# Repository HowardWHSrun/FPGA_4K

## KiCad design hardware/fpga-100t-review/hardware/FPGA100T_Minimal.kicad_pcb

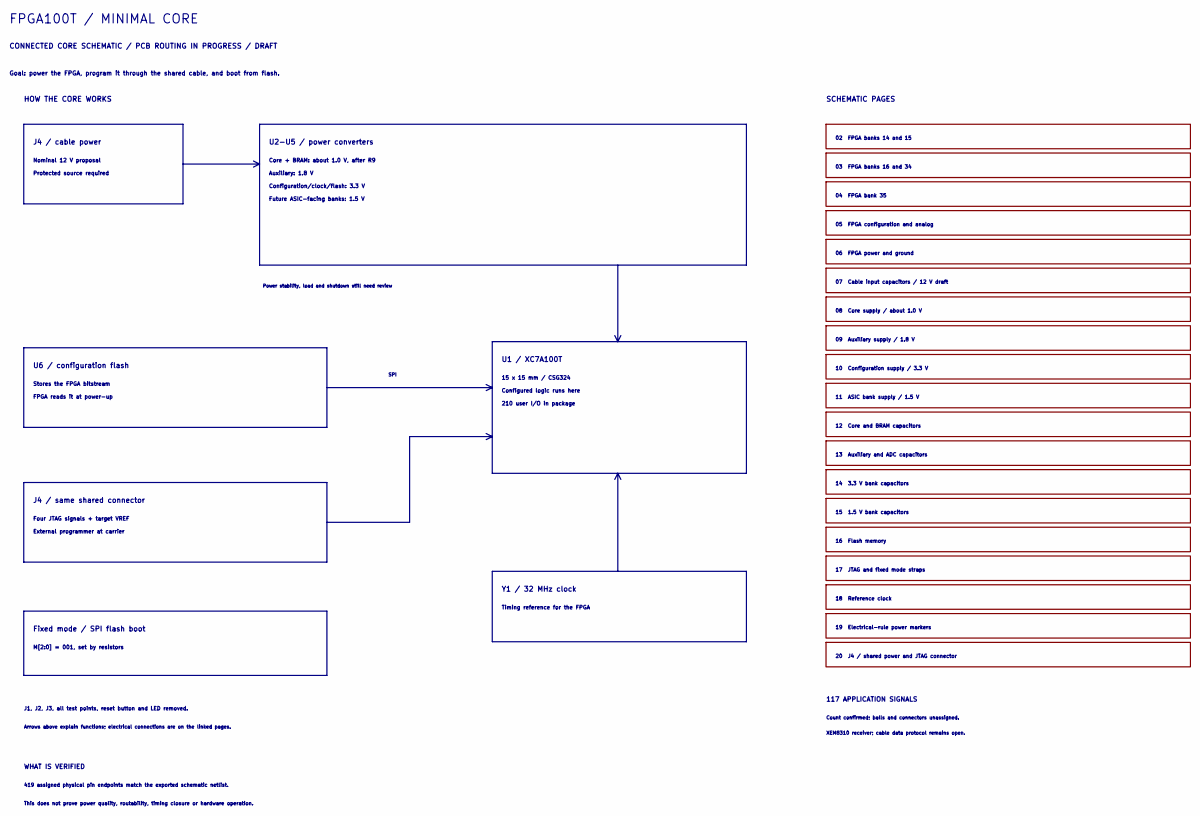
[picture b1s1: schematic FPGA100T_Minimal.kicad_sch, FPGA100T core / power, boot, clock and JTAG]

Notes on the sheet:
FPGA100T / MINIMAL CORE
CONNECTED CORE SCHEMATIC / PCB ROUTING IN PROGRESS / DRAFT
Goal: power the FPGA, program it through the shared cable, and boot from flash.
HOW THE CORE WORKS
J4 / cable power
Nominal 12 V proposal
Protected source required
U2-U5 / power converters
Core + BRAM: about 1.0 V, after R9
Auxiliary: 1.8 V
Configuration/clock/flash: 3.3 V
Future ASIC-facing banks: 1.5 V
Power stability, load and shutdown still need review
U1 / XC7A100T
15 x 15 mm / CSG324
Configured logic runs here
210 user I/O in package
U6 / configuration flash
Stores the FPGA bitstream
FPGA reads it at power-up
SPI
J4 / same shared connector
Four JTAG signals + target VREF
External programmer at carrier
Y1 / 32 MHz clock
Timing reference for the FPGA
Fixed mode / SPI flash boot
M[2:0] = 001, set by resistors
J1, J2, J3, all test points, reset button and LED removed.
Arrows above explain functions; electrical connections are on the linked pages.
WHAT IS VERIFIED
419 assigned physical pin endpoints match the exported schematic netlist.
This does not prove power quality, routability, timing closure or hardware operation.
SCHEMATIC PAGES
02 FPGA banks 14 and 15
03 FPGA banks 16 and 34
04 FPGA bank 35
05 FPGA configuration and analog
06 FPGA power and ground
07 Cable input capacitors / 12 V draft

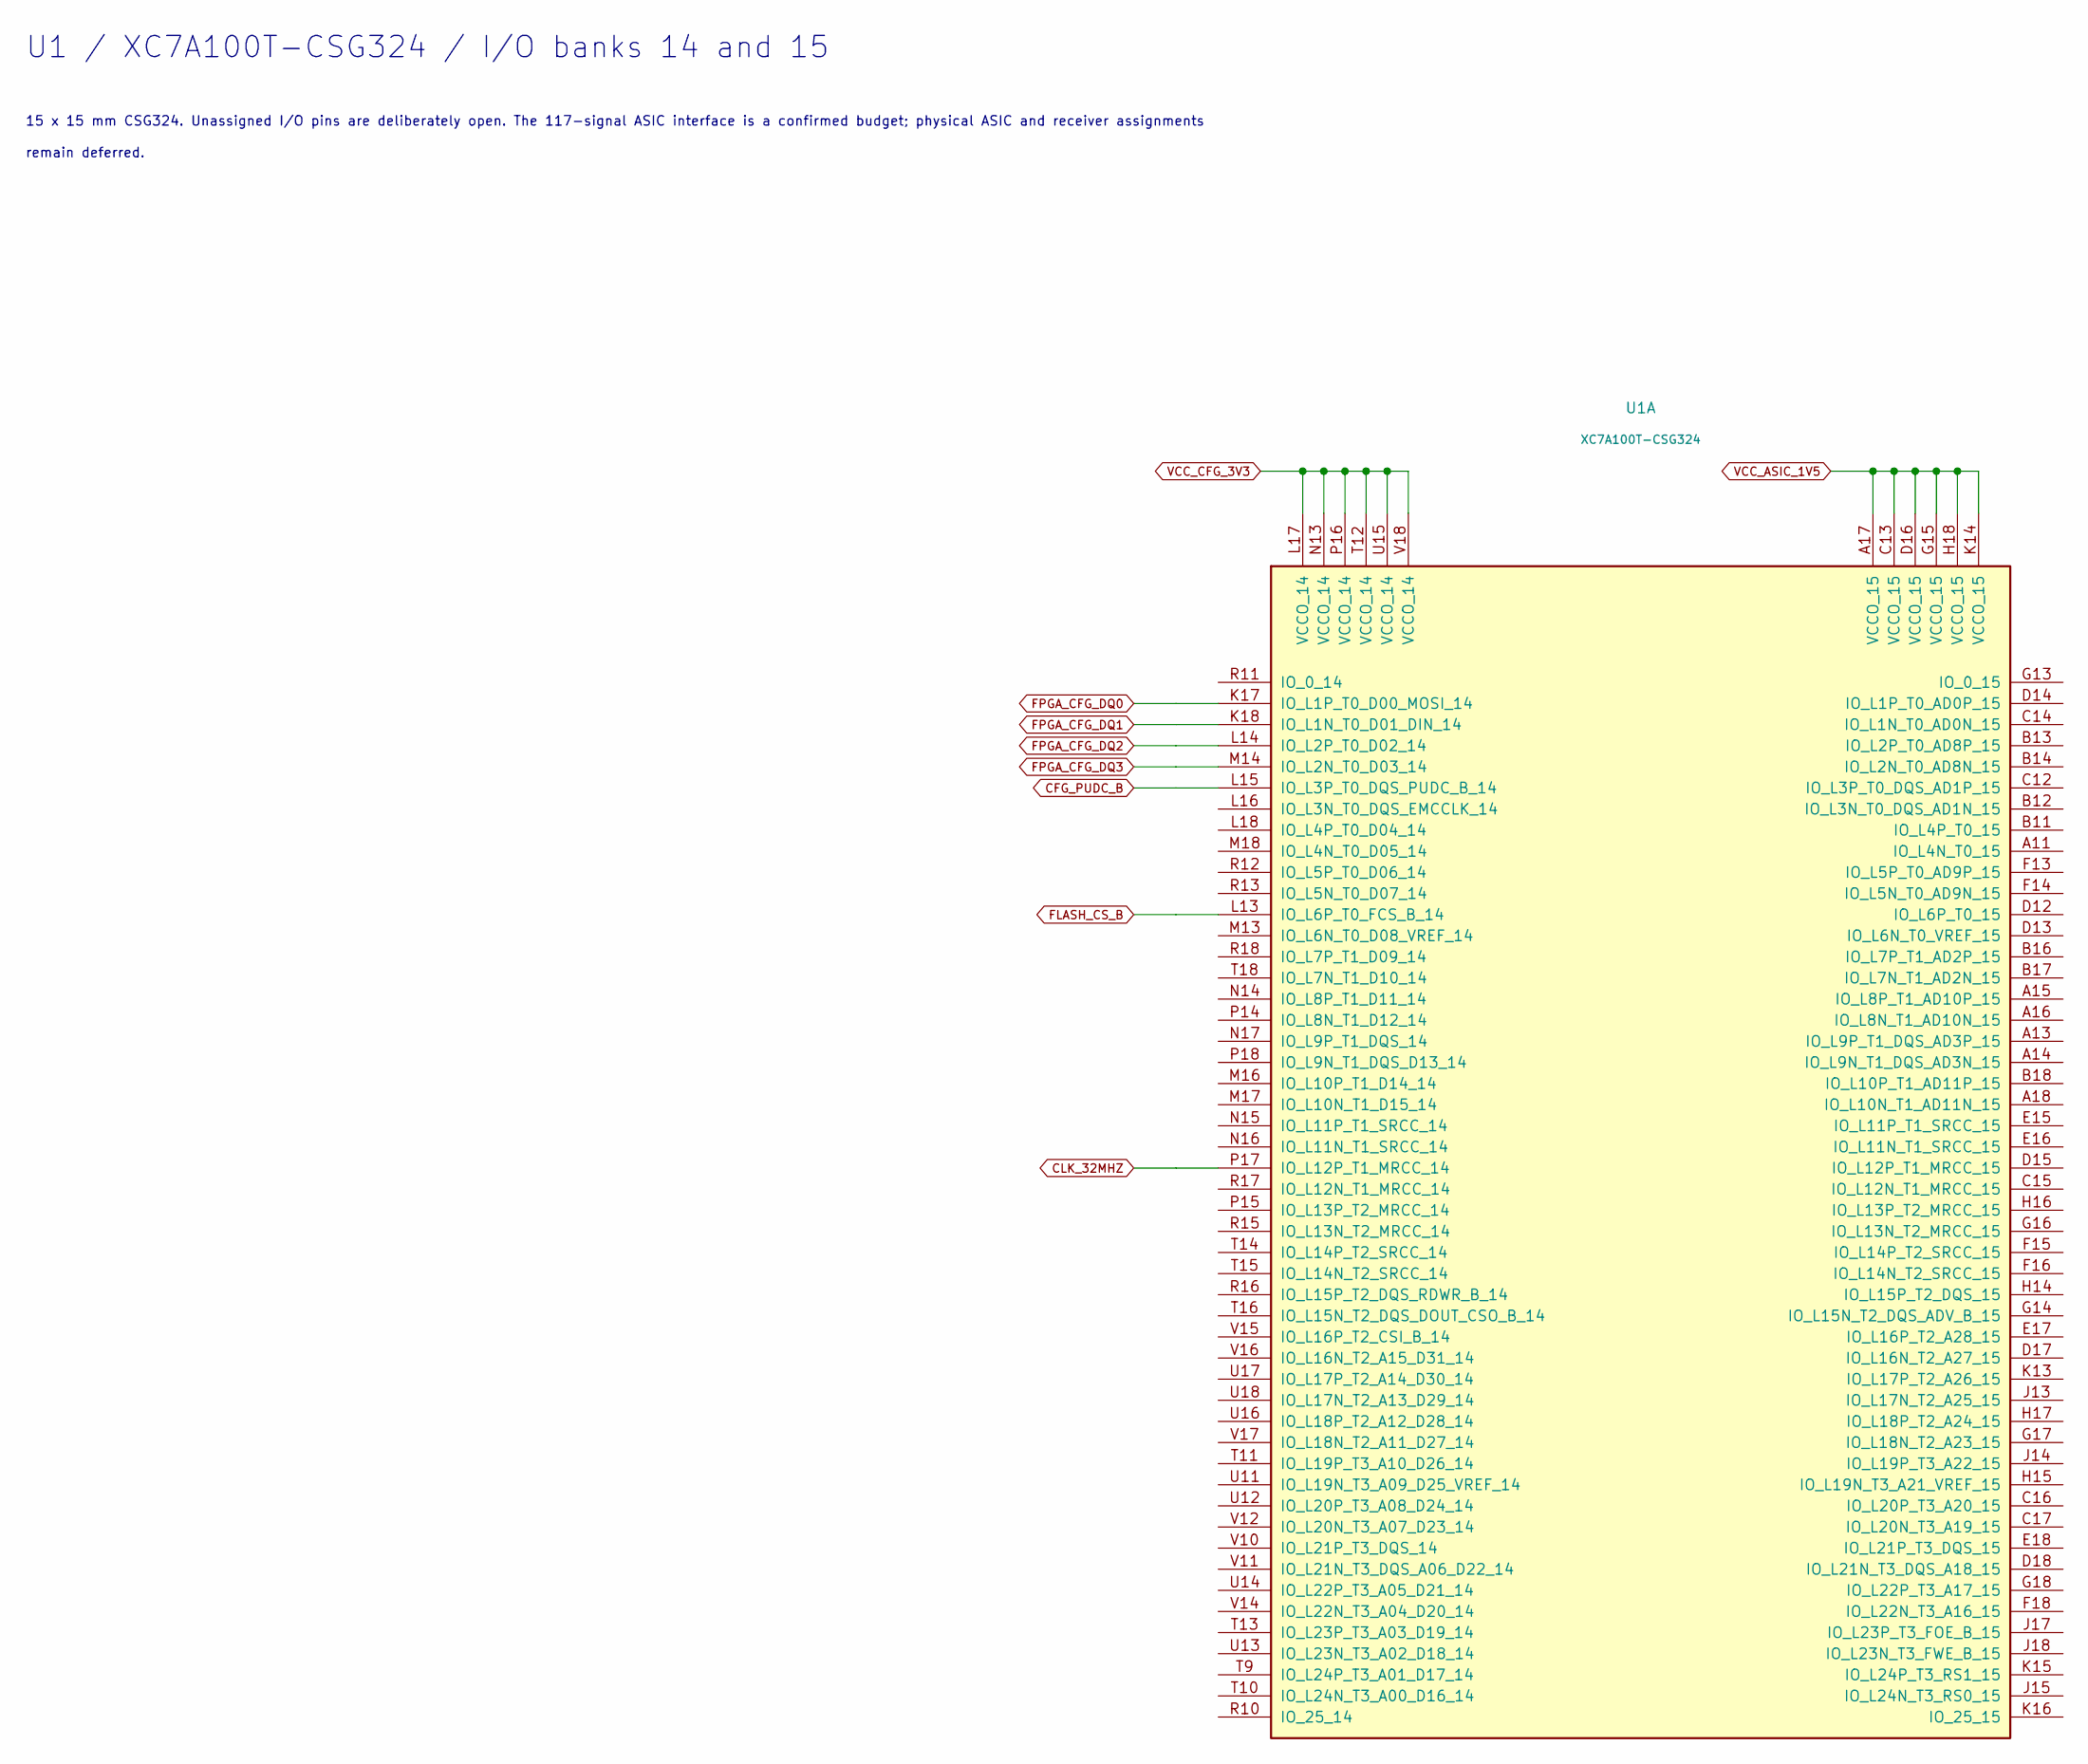
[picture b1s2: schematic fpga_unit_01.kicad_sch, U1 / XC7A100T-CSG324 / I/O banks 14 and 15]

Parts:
U1: XC7A100T-CSG324; Xilinx_CSG324; MPN XC7A100T — speed and temperature grade 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

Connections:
CFG_PUDC_B: U1.L15 (IO_L3P_T0_DQS_PUDC_B_14); also elsewhere on the board
CLK_32MHZ: U1.P17 (IO_L12P_T1_MRCC_14); also elsewhere on the board
FLASH_CS_B: U1.L13 (IO_L6P_T0_FCS_B_14); also elsewhere on the board
FPGA_CFG_DQ0: U1.K17 (IO_L1P_T0_D00_MOSI_14); also elsewhere on the board
FPGA_CFG_DQ1: U1.K18 (IO_L1N_T0_D01_DIN_14); also elsewhere on the board
FPGA_CFG_DQ2: U1.L14 (IO_L2P_T0_D02_14); also elsewhere on the board
FPGA_CFG_DQ3: U1.M14 (IO_L2N_T0_D03_14); also elsewhere on the board
VCC_ASIC_1V5: U1.A17 (VCCO_15), U1.C13 (VCCO_15), U1.D16 (VCCO_15), U1.G15 (VCCO_15), U1.H18 (VCCO_15), U1.K14 (VCCO_15); also elsewhere on the board
VCC_CFG_3V3: U1.L17 (VCCO_14), U1.N13 (VCCO_14), U1.P16 (VCCO_14), U1.T12 (VCCO_14), U1.U15 (VCCO_14), U1.V18 (VCCO_14); also elsewhere on the board

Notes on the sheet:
U1 / XC7A100T-CSG324 / I/O banks 14 and 15
15 x 15 mm CSG324. Unassigned I/O pins are deliberately open. The 117-signal ASIC interface is a confirmed budget; physical ASIC and receiver assignments
remain deferred.

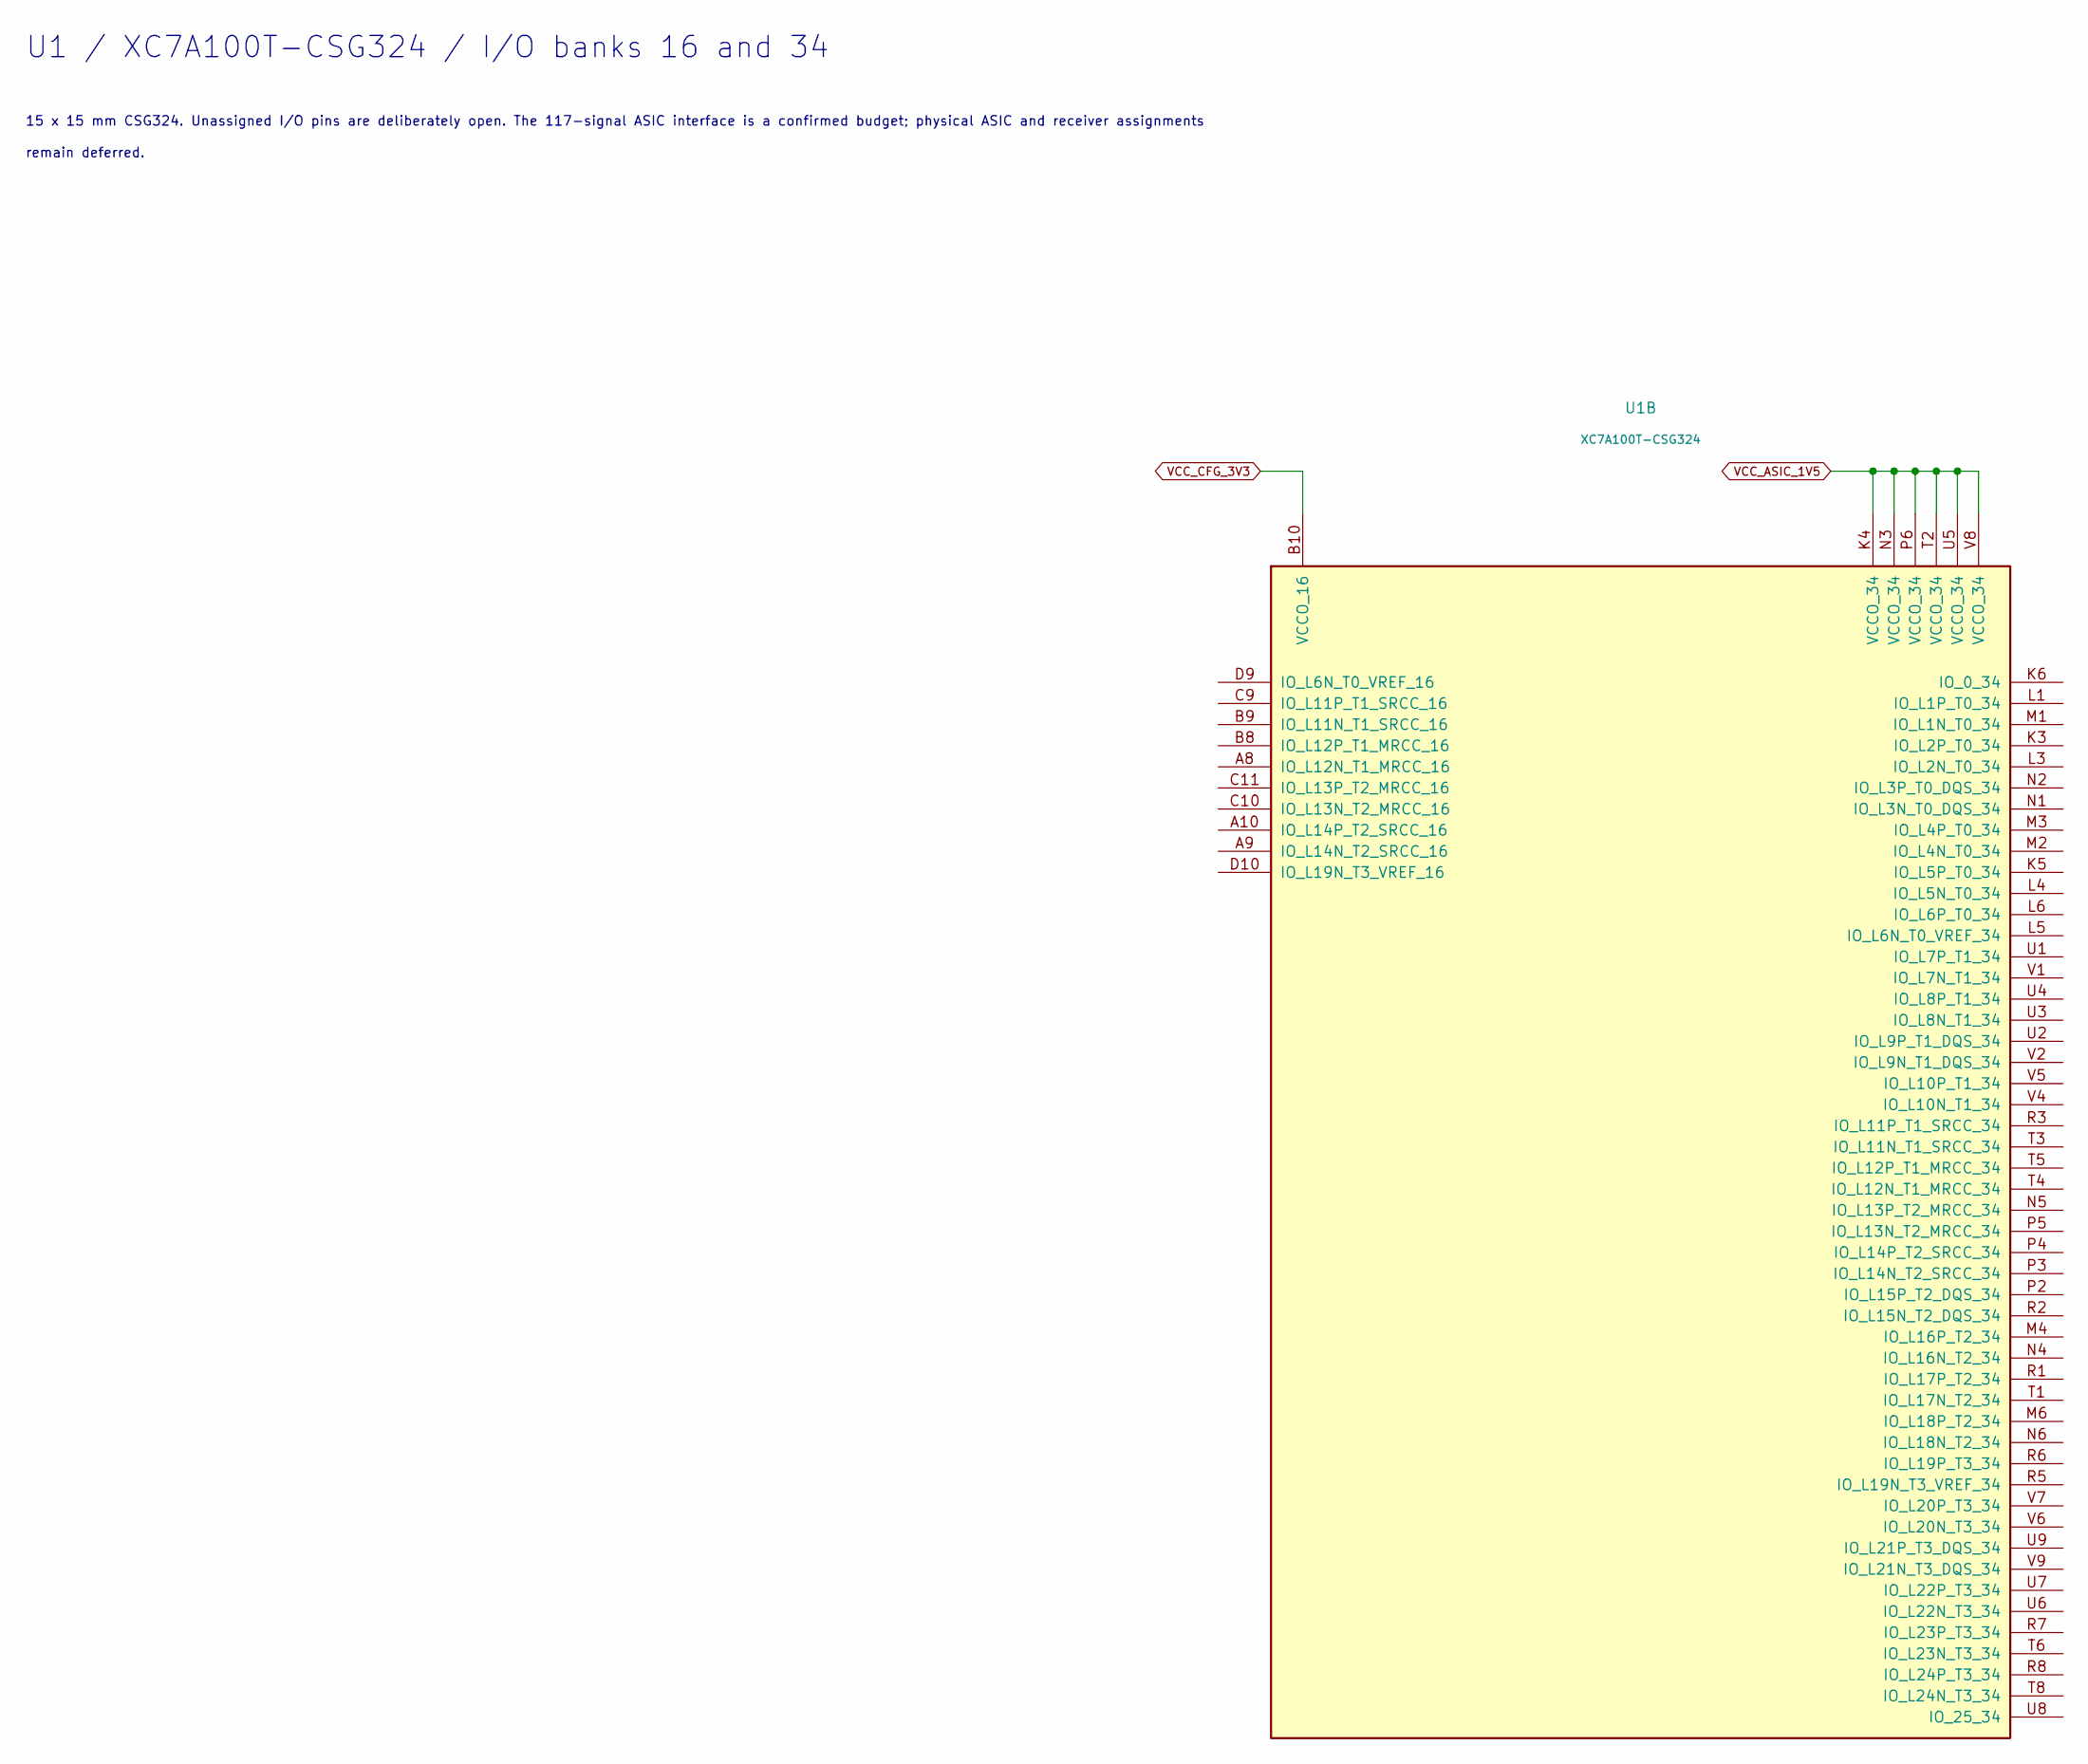
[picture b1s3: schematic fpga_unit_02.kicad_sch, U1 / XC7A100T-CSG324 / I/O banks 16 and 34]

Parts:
U1: XC7A100T-CSG324; Xilinx_CSG324; MPN XC7A100T — speed and temperature grade 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

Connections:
VCC_ASIC_1V5: U1.K4 (VCCO_34), U1.N3 (VCCO_34), U1.P6 (VCCO_34), U1.T2 (VCCO_34), U1.U5 (VCCO_34), U1.V8 (VCCO_34); also elsewhere on the board
VCC_CFG_3V3: U1.B10 (VCCO_16); also elsewhere on the board

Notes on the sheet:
U1 / XC7A100T-CSG324 / I/O banks 16 and 34
15 x 15 mm CSG324. Unassigned I/O pins are deliberately open. The 117-signal ASIC interface is a confirmed budget; physical ASIC and receiver assignments
remain deferred.

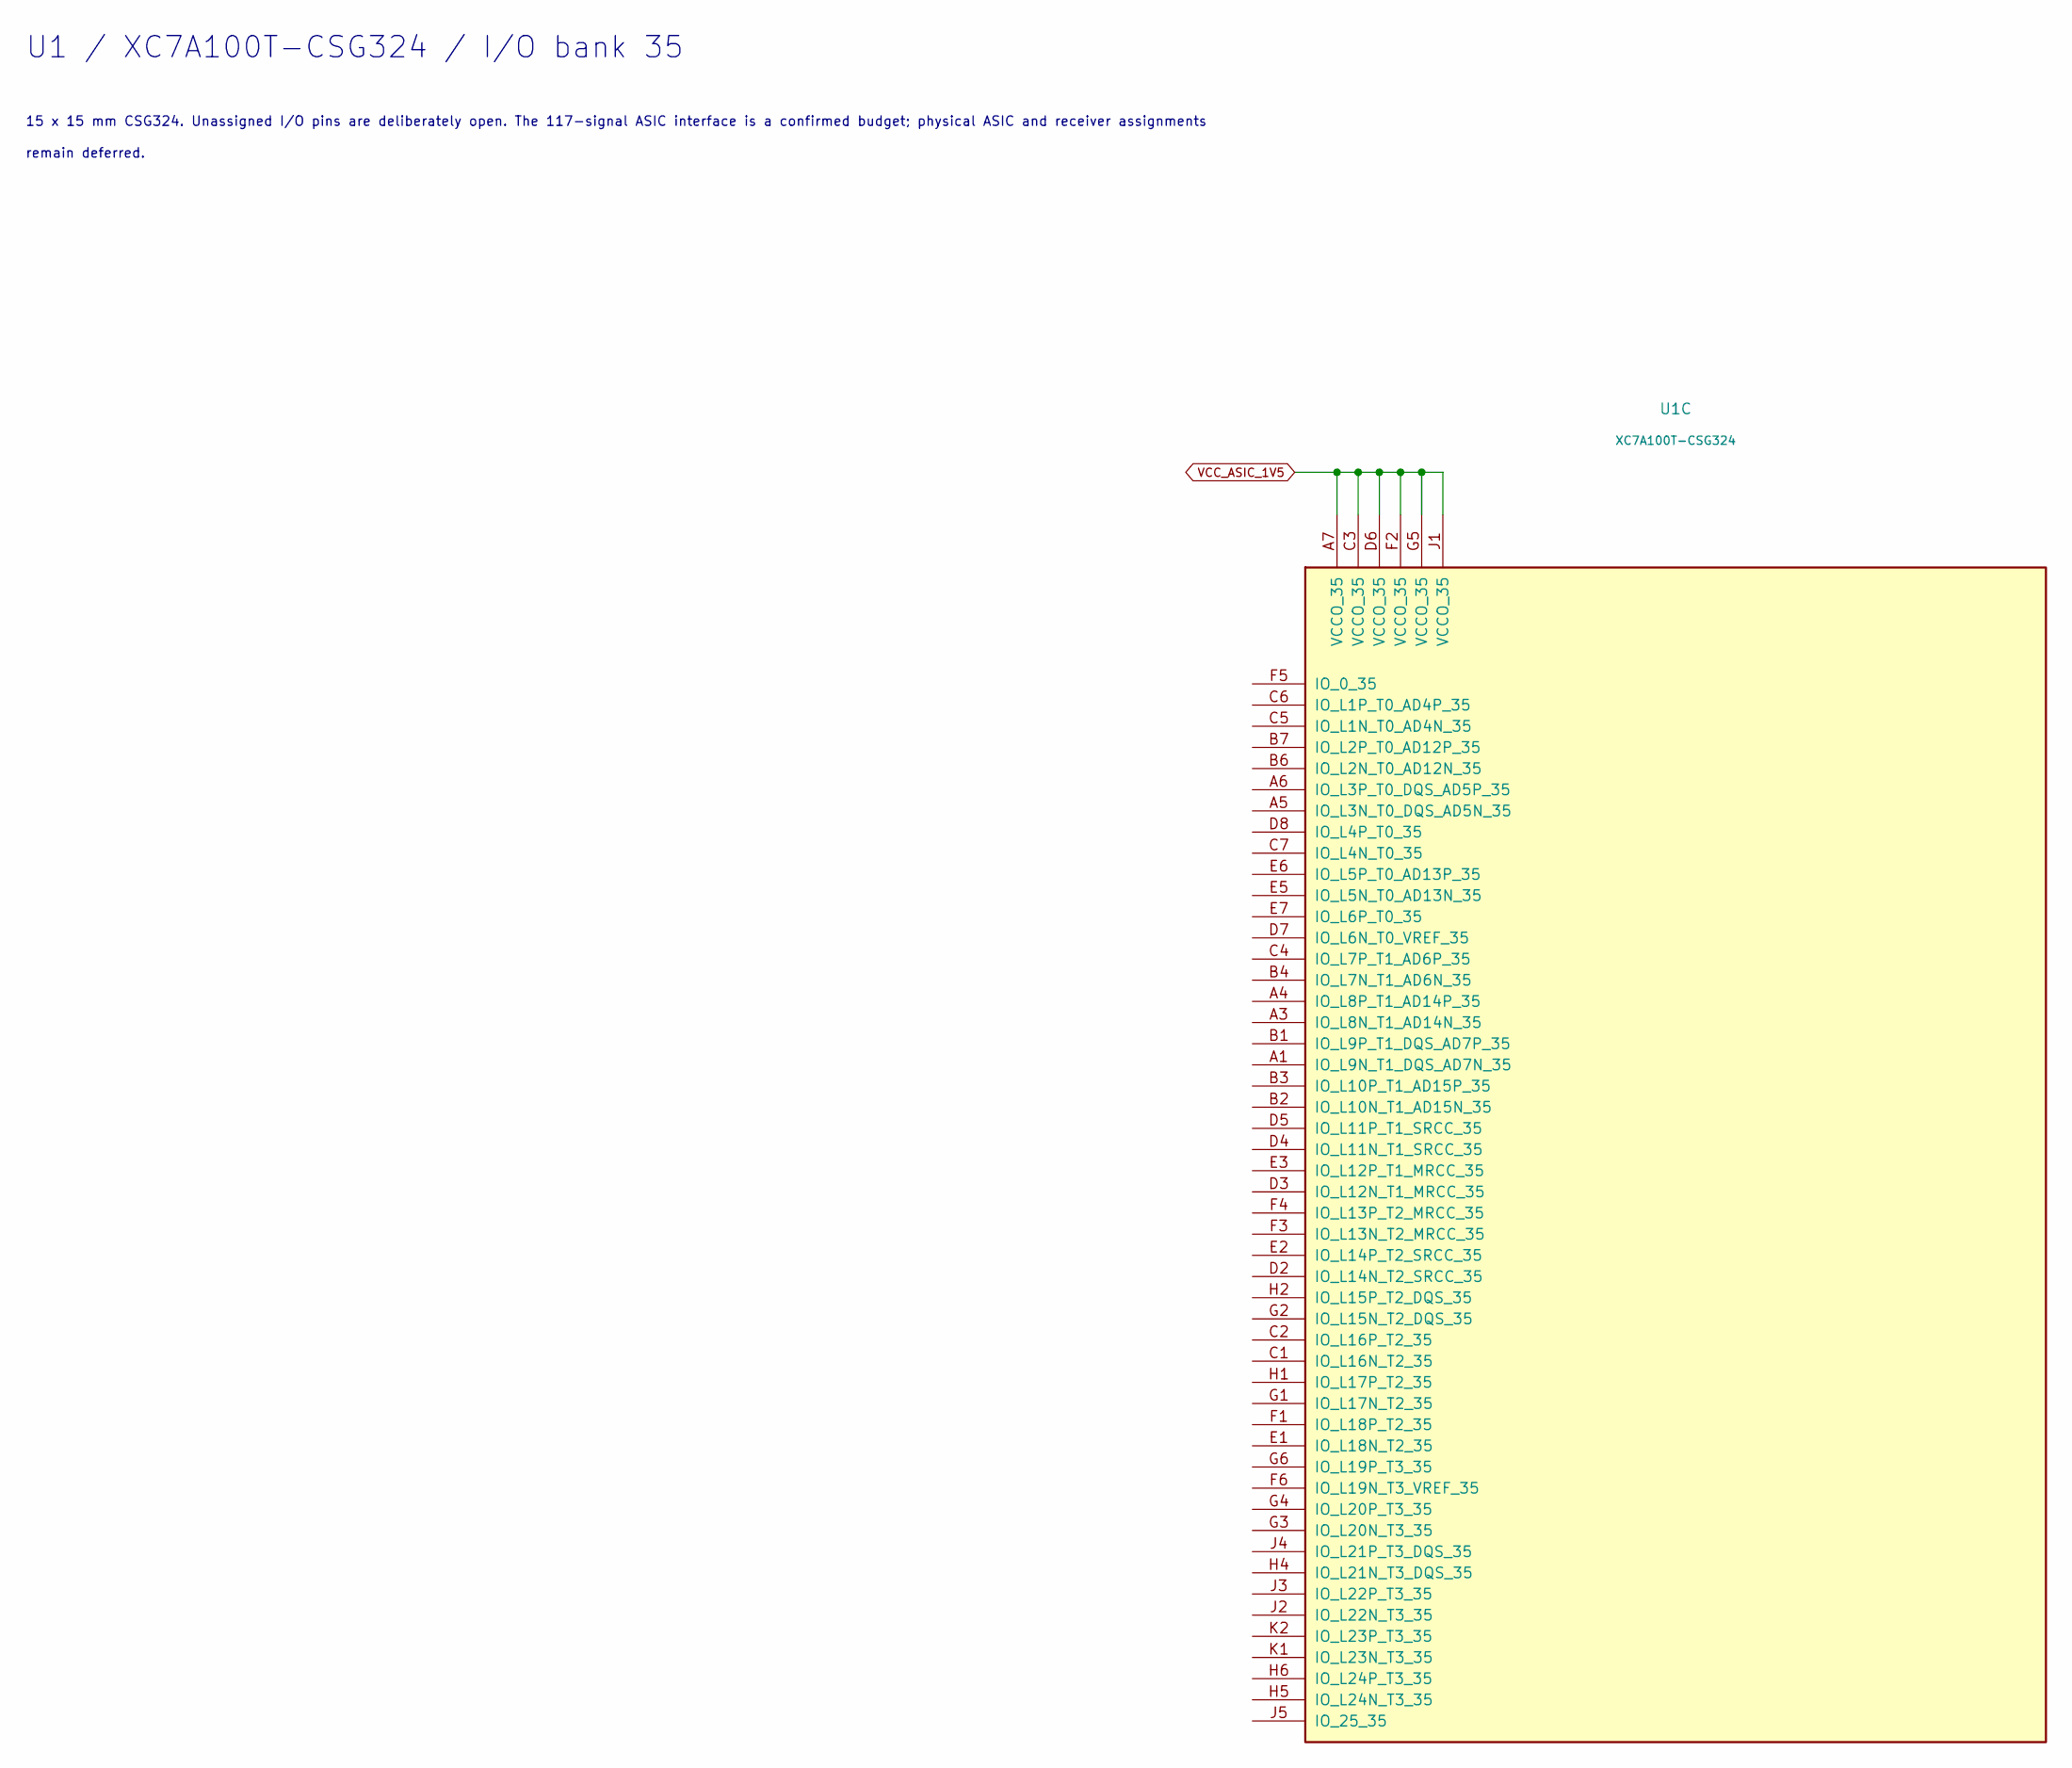
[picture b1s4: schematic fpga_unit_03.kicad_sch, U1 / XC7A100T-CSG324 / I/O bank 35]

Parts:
U1: XC7A100T-CSG324; Xilinx_CSG324; MPN XC7A100T — speed and temperature grade 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

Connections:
VCC_ASIC_1V5: U1.A7 (VCCO_35), U1.C3 (VCCO_35), U1.D6 (VCCO_35), U1.F2 (VCCO_35), U1.G5 (VCCO_35), U1.J1 (VCCO_35); also elsewhere on the board

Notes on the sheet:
U1 / XC7A100T-CSG324 / I/O bank 35
15 x 15 mm CSG324. Unassigned I/O pins are deliberately open. The 117-signal ASIC interface is a confirmed budget; physical ASIC and receiver assignments
remain deferred.

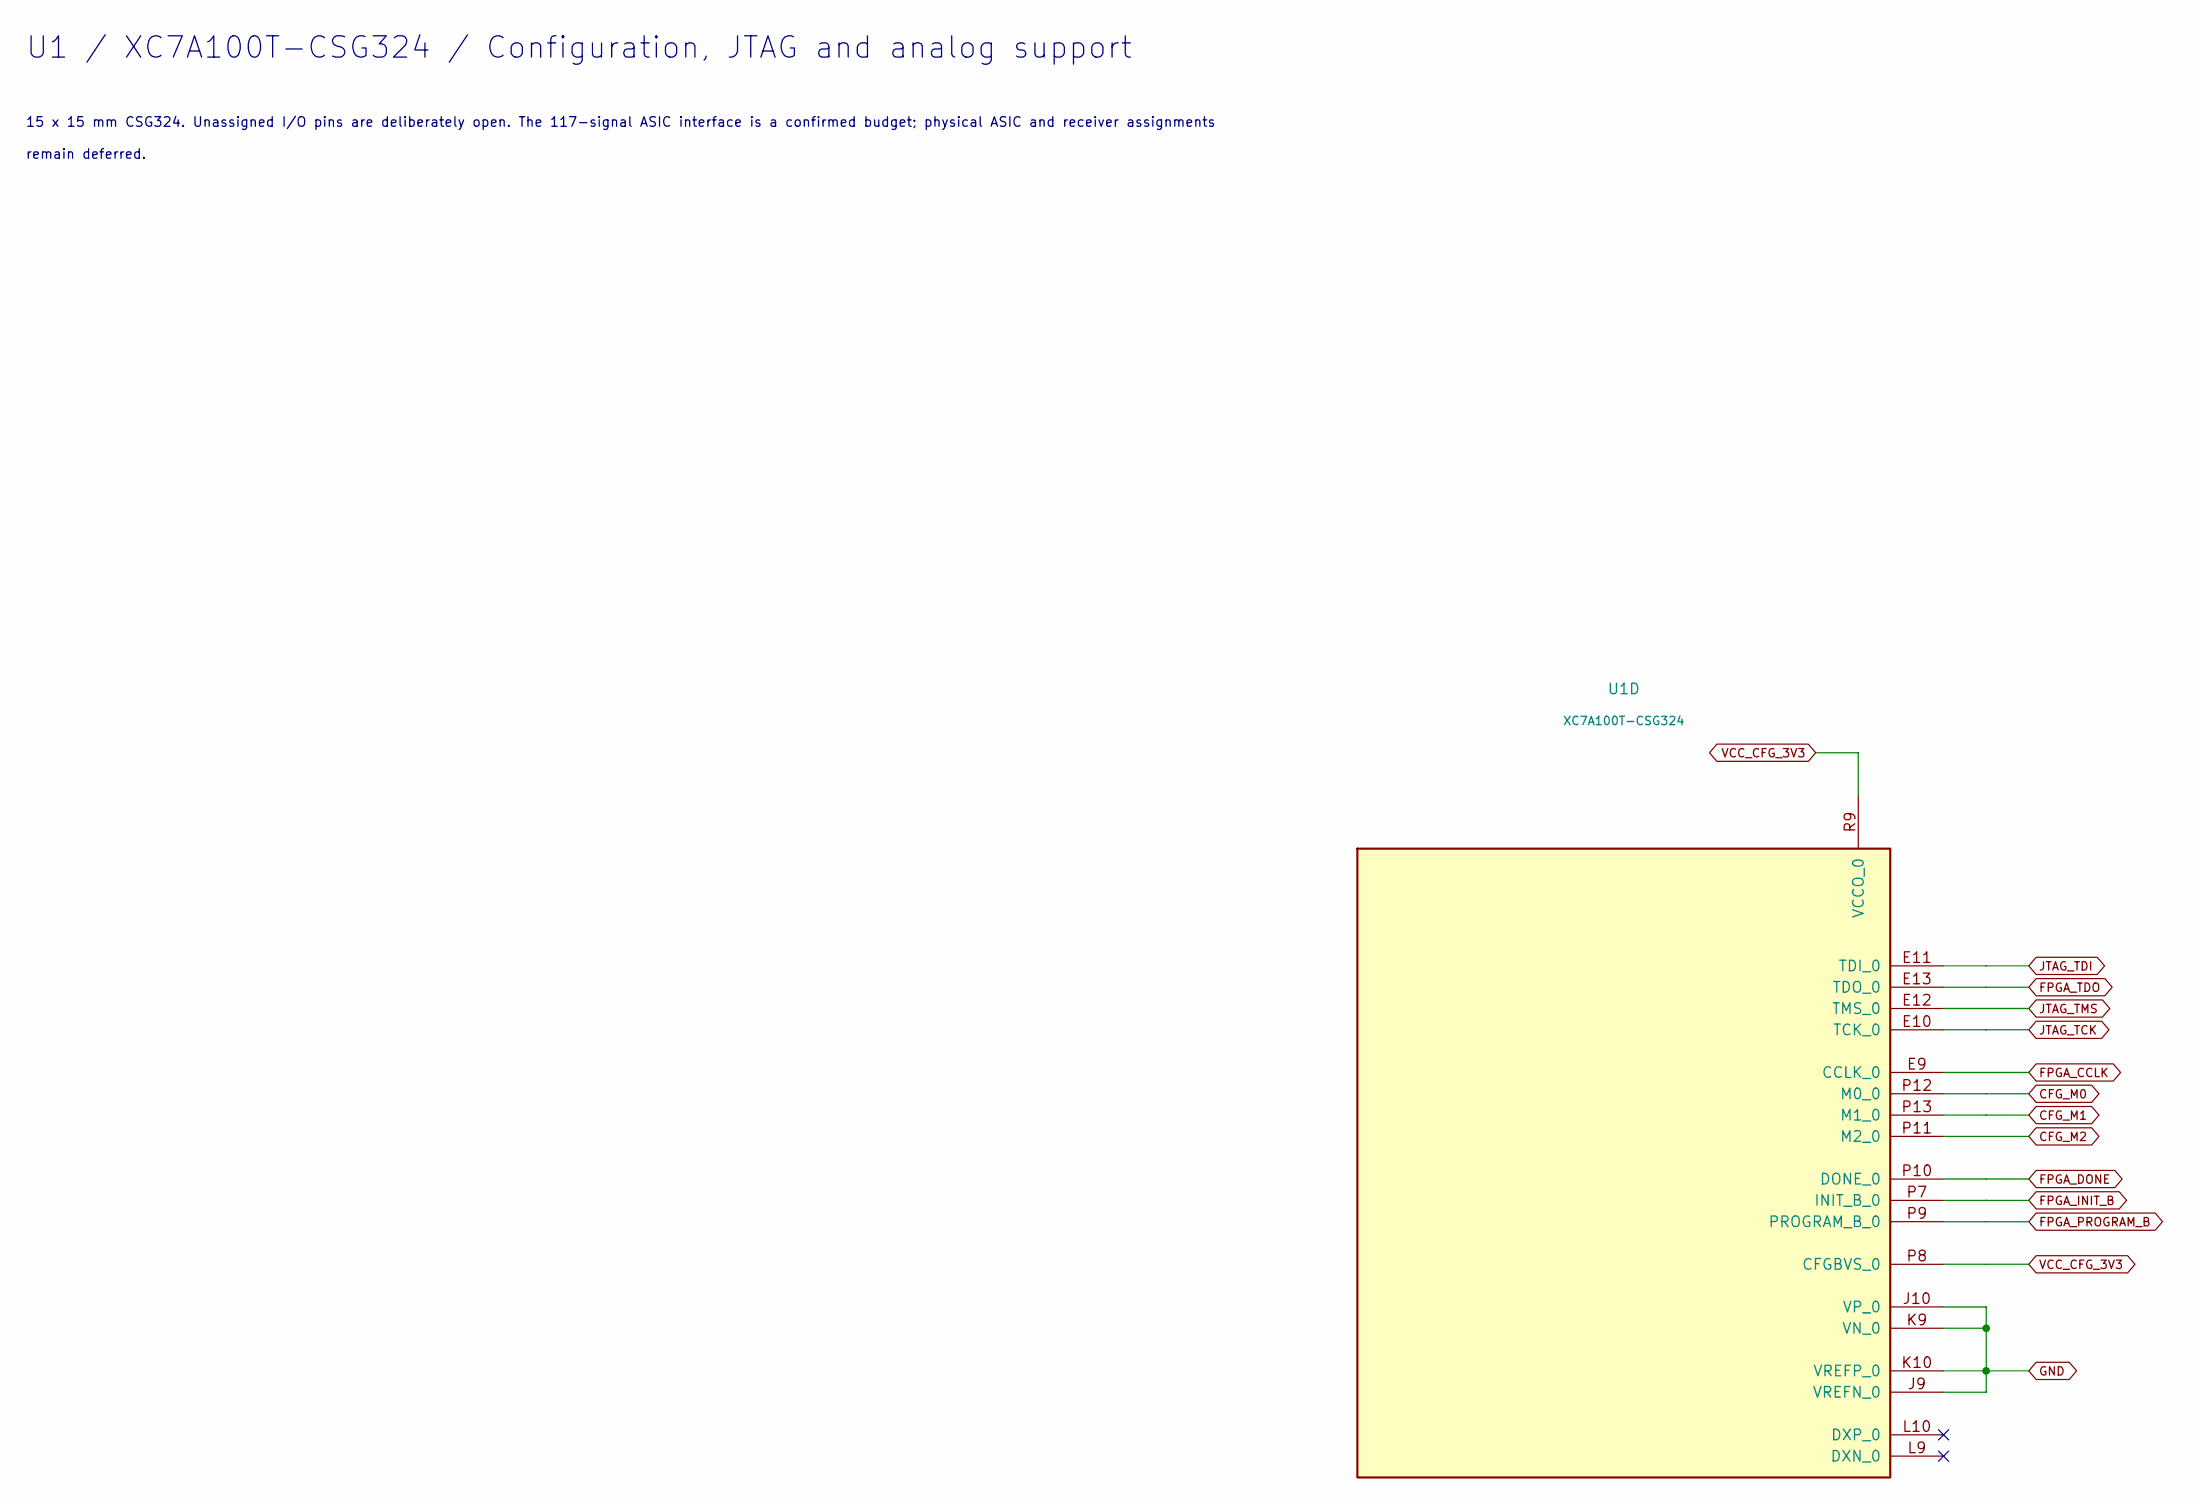
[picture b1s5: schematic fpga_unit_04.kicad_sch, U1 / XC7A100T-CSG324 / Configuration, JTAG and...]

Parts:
U1: XC7A100T-CSG324; Xilinx_CSG324; MPN XC7A100T — speed and temperature grade 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

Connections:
CFG_M0: U1.P12 (M0_0); also elsewhere on the board
CFG_M1: U1.P13 (M1_0); also elsewhere on the board
CFG_M2: U1.P11 (M2_0); also elsewhere on the board
FPGA_CCLK: U1.E9 (CCLK_0); also elsewhere on the board
FPGA_DONE: U1.P10 (DONE_0); also elsewhere on the board
FPGA_INIT_B: U1.P7 (INIT_B_0); also elsewhere on the board
FPGA_PROGRAM_B: U1.P9 (PROGRAM_B_0); also elsewhere on the board
FPGA_TDO: U1.E13 (TDO_0); also elsewhere on the board
GND: U1.J9 (VREFN_0), U1.J10 (VP_0), U1.K9 (VN_0), U1.K10 (VREFP_0); also elsewhere on the board
JTAG_TCK: U1.E10 (TCK_0); also elsewhere on the board
JTAG_TDI: U1.E11 (TDI_0); also elsewhere on the board
JTAG_TMS: U1.E12 (TMS_0); also elsewhere on the board
VCC_CFG_3V3: U1.P8 (CFGBVS_0), U1.R9 (VCCO_0); also elsewhere on the board

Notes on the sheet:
U1 / XC7A100T-CSG324 / Configuration, JTAG and analog support
15 x 15 mm CSG324. Unassigned I/O pins are deliberately open. The 117-signal ASIC interface is a confirmed budget; physical ASIC and receiver assignments
remain deferred.
